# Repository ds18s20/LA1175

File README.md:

# LA1175
FM- tuner using LA1175/ KiCad project

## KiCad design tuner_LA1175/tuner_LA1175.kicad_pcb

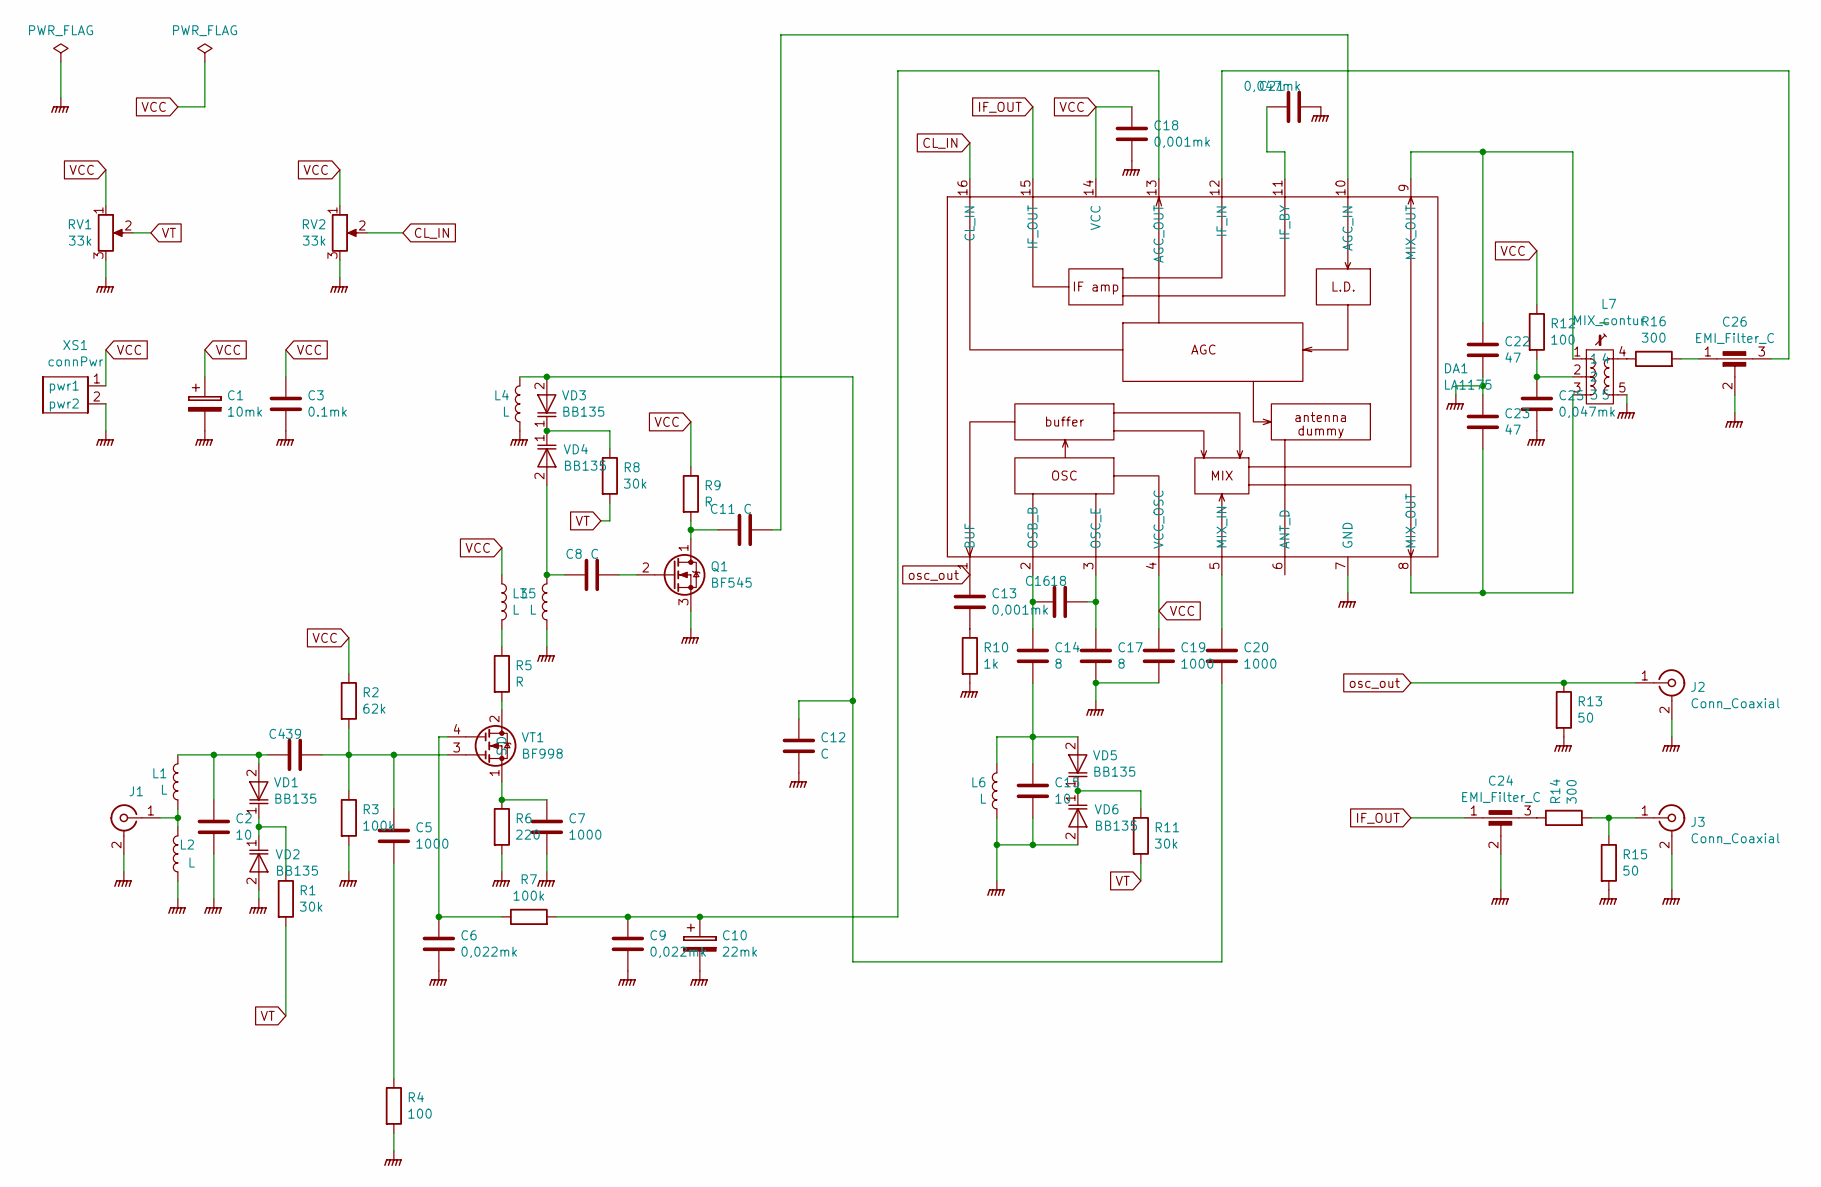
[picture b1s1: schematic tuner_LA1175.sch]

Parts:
C1: 10mk; CP_EIA-3528-21_Kemet-B_Pad1.50x2.35mm_HandSolder
C2, C15: 10; C_0805_2012Metric
C3: 0.1mk; C_0805_2012Metric
C4: 39; C_0805_2012Metric
C5, C7, C19, C20: 1000; C_0805_2012Metric
C6, C9: 0,022mk; C_0805_2012Metric
C8, C11, C12: C; C_0805_2012Metric
C10: 22mk; CP_EIA-3528-21_Kemet-B_Pad1.50x2.35mm_HandSolder
C13, C18: 0,001mk; C_0805_2012Metric
C14, C17: 8; C_0805_2012Metric
C16: 18; C_0805_2012Metric
C21, C25: 0,047mk; C_0805_2012Metric
C22, C23: 47; C_0805_2012Metric
C24, C26: EMI_Filter_C; sfe10.7
DA1: LA1175; SOIC-16W_5.3x10.2mm_P1.27mm
J1, J2, J3: Conn_Coaxial; SMA_Molex_73251-2120_EdgeMount_Horizontal
L1, L2, L4, L5, L6: L; air_coil
L3: L; L_0805_2012Metric_Pad1.15x1.40mm_HandSolder
L7: MIX_contur; mix_coil
Q1: BF545; SOT-23_Handsoldering
R1, R8, R11: 30k; R_0805_2012Metric
R2: 62k; R_0805_2012Metric
R3, R7: 100k; R_0805_2012Metric
R4, R12: 100; R_0805_2012Metric
R5, R9: R; R_0805_2012Metric
R6: 220; R_0805_2012Metric
R10: 1k; R_0805_2012Metric
R13, R15: 50; R_0805_2012Metric
R14, R16: 300; R_0805_2012Metric
RV1, RV2: 33k; sp3--33B
VD1, VD2, VD3, VD4, VD5, VD6: BB135; SOD-323
VT1: BF998; SOT-143
XS1: connPwr; conn_pwr

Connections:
CL_IN: DA1.16 (CL_IN), RV2.2
GNDPWR: C1.2, C2.2, C3.2, C6.2, C7.2, C9.2, C10.2, C12.2, C15.2, C17.2, C18.2, C19.2, C21.2, C22.2, C23.1, C24.2, C25.2, C26.2, DA1.7 (GND), J1.2 (Ext), J2.2 (Ext), J3.2 (Ext), L2.2, L4.2, L5.2, L6.2, L7.5, L7.6 (GNDPWR), L7.7 (GNDPWR), Q1.3 (S), R3.2, R4.2, R6.2, R10.2, R13.2, R15.2, RV1.3, RV2.3, VD2.2, VD6.2, XS1.2 (pwr2)
IF_OUT: C24.1, DA1.15 (IF_OUT)
unnamed: C2.1, C4.1, L1.1, VD1.2
unnamed: C4.2, C5.1, R2.2, R3.1, VT1.3
unnamed: C5.2, R4.1
unnamed: C6.1, R7.1, VT1.4
unnamed: C7.1, R6.1, VT1.1 (S)
unnamed: C8.1, L5.1, VD4.2
unnamed: C8.2, Q1.2 (G)
unnamed: C9.1, C10.1, DA1.13 (AGC_OUT), R7.2
unnamed: C11.1, Q1.1 (D), R9.2
unnamed: C11.2, DA1.10 (AGC_IN)
unnamed: C12.1, C20.2, L4.1, VD3.2
unnamed: C13.2, R10.1
unnamed: C14.1, C16.1, DA1.2 (OSB_B)
unnamed: C14.2, C15.1, L6.1, VD5.2
unnamed: C16.2, C17.1, DA1.3 (OSC_E)
unnamed: C20.1, DA1.5 (MIX_IN)
unnamed: C21.1, DA1.11 (IF_BY)
unnamed: C22.1, DA1.9 (MIX_OUT), L7.1
unnamed: C23.2, DA1.8 (MIX_OUT), L7.3
unnamed: C24.3, R14.1
unnamed: C25.1, L7.2, R12.2
unnamed: C26.1, R16.2
unnamed: C26.3, DA1.12 (IF_IN)
unnamed: J1.1 (In), L1.2, L2.1
unnamed: J3.1 (In), R14.2, R15.1
unnamed: L3.2, R5.1
unnamed: L7.4, R16.1
unnamed: R1.1, VD1.1, VD2.1
unnamed: R5.2, VT1.2 (D)
unnamed: R8.1, VD3.1, VD4.1
unnamed: R11.1, VD5.1, VD6.1
VCC: C1.1, C3.1, C18.1, C19.1, DA1.4 (VCC_OSC), DA1.14 (VCC), L3.1, R2.1, R9.1, R12.1, RV1.1, RV2.1, XS1.1 (pwr1)
VT: R1.2, R8.2, R11.2, RV1.2
osc_out: C13.1, DA1.1 (BUF), J2.1 (In), R13.1

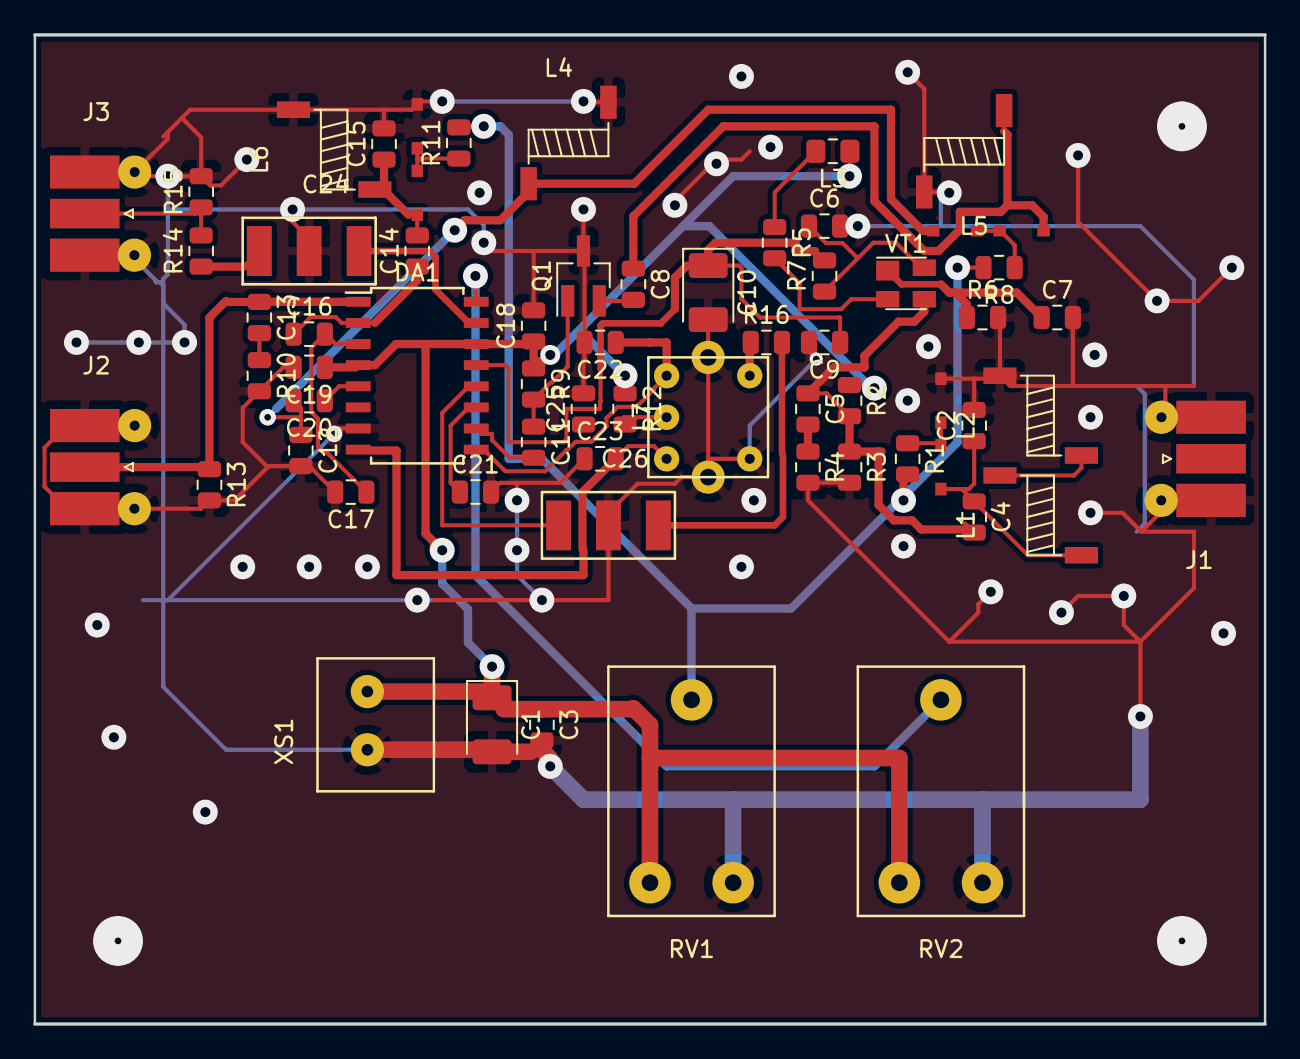
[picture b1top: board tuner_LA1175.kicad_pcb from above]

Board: 2 copper layers, 74.0 x 59.5 mm, 64 parts (0 on the bottom side), 37 nets.

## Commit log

2020-10-31 Init
2020-10-31 Del 123
